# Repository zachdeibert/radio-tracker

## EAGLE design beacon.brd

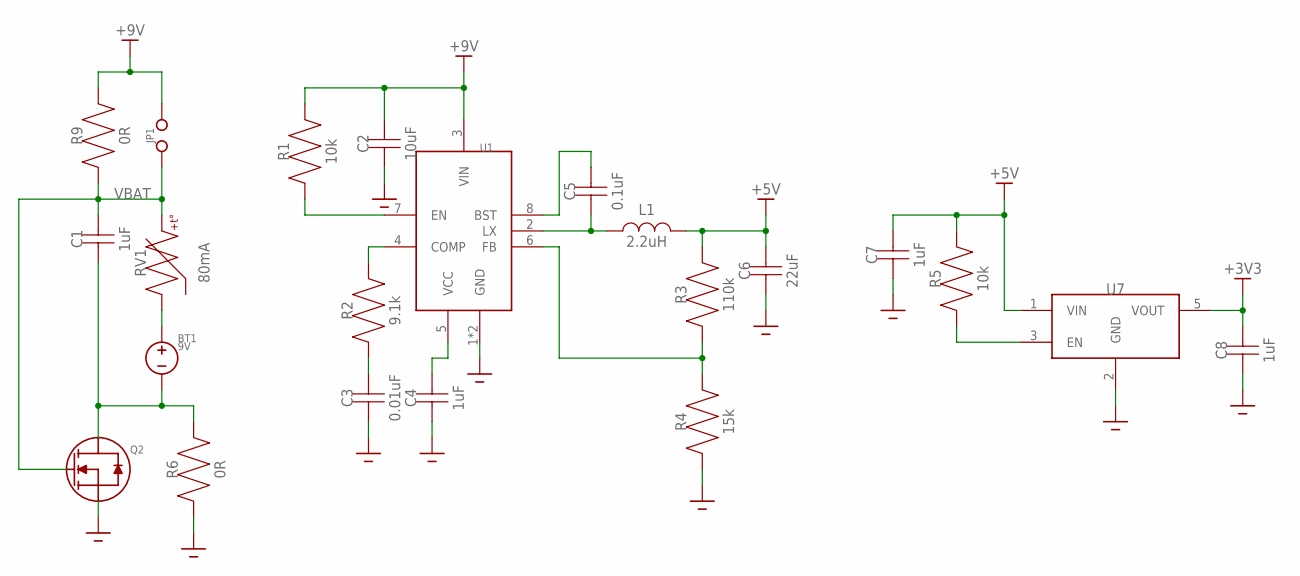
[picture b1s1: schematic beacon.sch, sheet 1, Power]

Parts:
BT1: 9V; JUMPER
C1, C4, C7, C8: 1uF; 0603
C2: 10uF; 0805
C3: 0.01uF; 0603
C5: 0.1uF; 0603
C6: 22uF; 0805
JP1: JUMPER
L1: 2.2uH; 0805
Q2: DMG2302UK
R1, R5: 10k; 0603
R2: 9.1k; 0603
R3: 110k; 0603
R4: 15k; 0603
R6, R9: 0R; 0805
RV1: 80mA; 0603
U1: AOZ6662DI
U7: MIC5504

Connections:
+3V3: C8.P$2, U7.5 (VOUT); also elsewhere on the board
+5V: C6.P$2, C7.P$2, L1.P$2, R3.P$2, R5.P$2, U7.1 (VIN); also elsewhere on the board
+9V: C2.P$2, JP1.2, R1.P$2, R9.P$2, U1.3 (VIN); also elsewhere on the board
GND: C2.P$1, C3.P$1, C4.P$1, C6.P$1, C7.P$1, C8.P$1, Q2.2 (S), R4.P$1, R6.P$1, U1.1 (GND), U1.9 (GND), U7.2 (GND); also elsewhere on the board
unnamed: R2.P$2, U1.4 (COMP)
unnamed: R1.P$1, U1.7 (EN)
unnamed: C3.P$2, R2.P$1
unnamed: C4.P$2, U1.5 (VCC)
unnamed: C5.P$2, U1.8 (BST)
unnamed: C5.P$1, L1.P$1, U1.2 (LX)
unnamed: R3.P$1, R4.P$2, U1.6 (FB)
unnamed: BT1.1, C1.P$1, Q2.3 (D), R6.P$2
unnamed: R5.P$1, U7.3 (EN)
unnamed: BT1.2, RV1.P$1
VBAT: C1.P$2, JP1.1, Q2.1 (G), R9.P$1, RV1.P$2; also elsewhere on the board

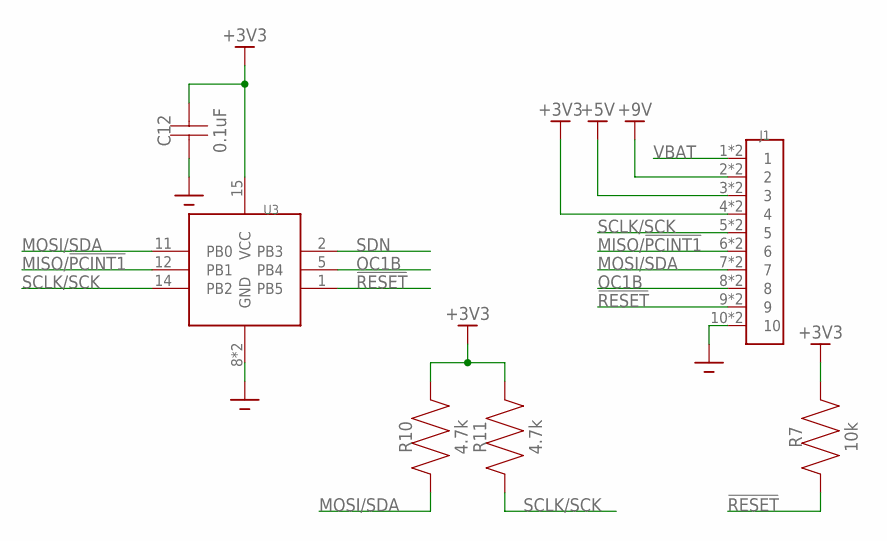
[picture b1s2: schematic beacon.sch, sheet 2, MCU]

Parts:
C12: 0.1uF; 0603
J1: 5-5530843-0MALE; 5-5530843-0-M
R7: 10k; 0603
R10, R11: 4.7k; 0603
U3: ATTINY85

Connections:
!RESET: J1.9, J1.19 (9), R7.P$1, U3.1 (PB5)
+3V3: C12.P$2, J1.4, J1.14 (4), R7.P$2, R10.P$2, R11.P$2, U3.15 (VCC); also elsewhere on the board
+5V: J1.3, J1.13 (3); also elsewhere on the board
+9V: J1.2, J1.12 (2); also elsewhere on the board
GND: C12.P$1, J1.10, J1.20 (10), U3.8 (GND), U3.21 (GND); also elsewhere on the board
MISO/!PCINT1: J1.6, J1.16 (6), U3.12 (PB1); also elsewhere on the board
MOSI/SDA: J1.7, J1.17 (7), R10.P$1, U3.11 (PB0); also elsewhere on the board
OC1B: J1.8, J1.18 (8), U3.5 (PB4); also elsewhere on the board
SCLK/SCK: J1.5, J1.15 (5), R11.P$1, U3.14 (PB2); also elsewhere on the board
SDN: U3.2 (PB3); also elsewhere on the board
VBAT: J1.1, J1.11 (1); also elsewhere on the board

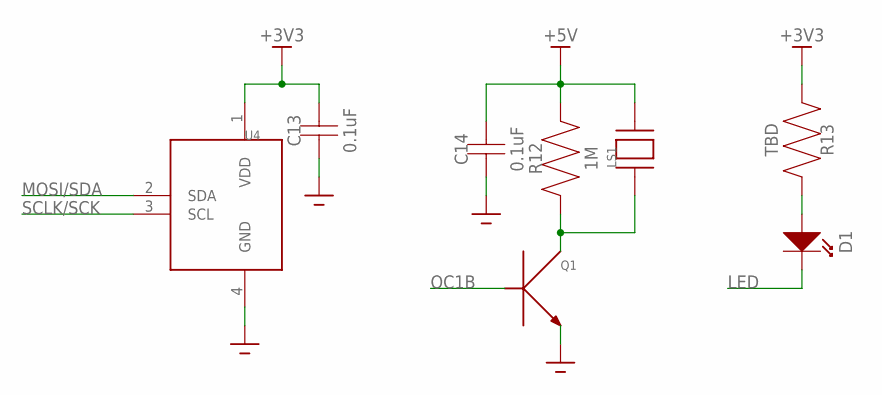
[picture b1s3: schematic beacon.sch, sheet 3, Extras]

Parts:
C13, C14: 0.1uF; 0603
D1: LED; 0805
LS1: AT-1224-TWT-5V-2-R
Q1: MMBT3904
R12: 1M; 0603
R13: TBD; 0603
U4: MS5637-02BA03

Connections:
+3V3: C13.P$2, R13.P$1, U4.1 (VDD); also elsewhere on the board
+5V: C14.P$2, LS1.2, R12.P$2; also elsewhere on the board
GND: C13.P$1, C14.P$1, Q1.2 (E), U4.4 (GND); also elsewhere on the board
LED: D1.P$2 (OUT); also elsewhere on the board
MOSI/SDA: U4.2 (SDA); also elsewhere on the board
unnamed: LS1.1, Q1.3 (C), R12.P$1
unnamed: D1.P$1 (IN), R13.P$2
OC1B: Q1.1 (B); also elsewhere on the board
SCLK/SCK: U4.3 (SCL); also elsewhere on the board

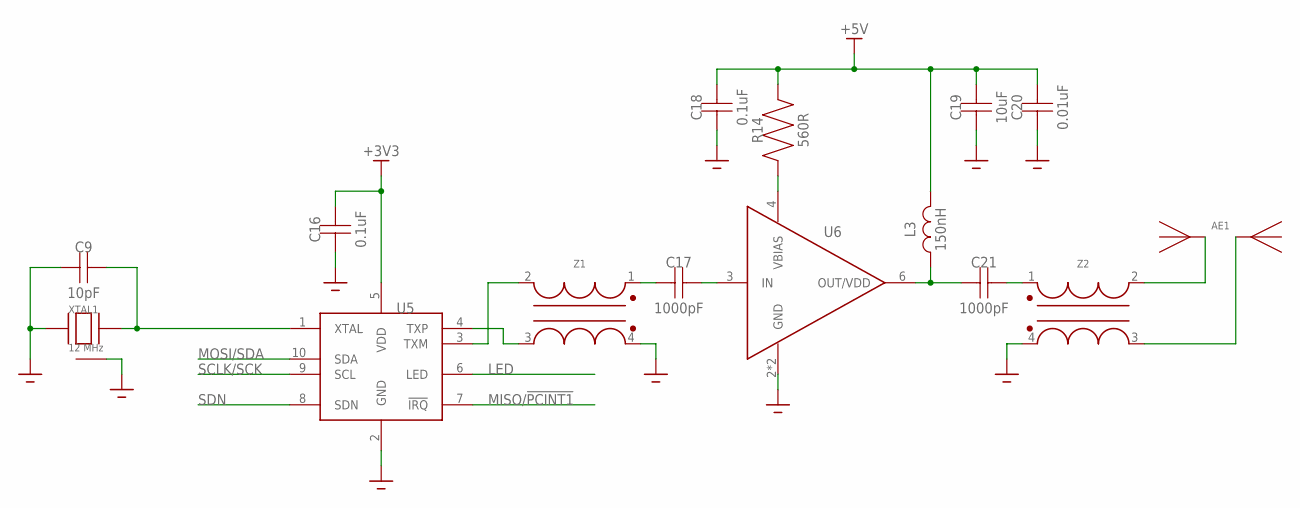
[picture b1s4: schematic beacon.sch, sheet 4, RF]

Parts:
AE1: ANTENNA
C9: 10pF; 0603
C16, C18: 0.1uF; 0603
C17, C21: 1000pF; 0402
C19: 10uF; 0603
C20: 0.01uF; 0603
L3: 150nH; 0402
R14: 560R; 0603
U5: SI4012
U6: MAAL-010704
XTAL1: 12 MHz; RH100
Z1, Z2: ABT-8

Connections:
+3V3: C16.P$2, U5.5 (VDD); also elsewhere on the board
+5V: C18.P$2, C19.P$2, C20.P$2, L3.2, R14.P$2; also elsewhere on the board
GND: C9.P$1, C16.P$1, C18.P$1, C19.P$1, C20.P$1, U5.2 (GND), U6.2 (GND), U6.5 (GND), XTAL1.1 (GND), XTAL1.2, XTAL1.3 (GND), Z1.4 (UN2), Z2.4 (UN2); also elsewhere on the board
LED: U5.6 (LED); also elsewhere on the board
MISO/!PCINT1: U5.7 (!IRQ); also elsewhere on the board
MOSI/SDA: U5.10 (SDA); also elsewhere on the board
unnamed: U5.4 (TXP), Z1.3 (BAL2)
unnamed: U5.3 (TXM), Z1.2 (BAL1)
unnamed: C9.P$2, U5.1 (XTAL), XTAL1.4
unnamed: C21.1, L3.1, U6.6 (OUT/VDD)
unnamed: C17.1, Z1.1 (UN1)
unnamed: C17.2, U6.3 (IN)
unnamed: R14.P$1, U6.4 (VBIAS)
unnamed: C21.2, Z2.1 (UN1)
unnamed: AE1.LB, AE1.LT, Z2.2 (BAL1)
unnamed: AE1.RB, AE1.RT, Z2.3 (BAL2)
SCLK/SCK: U5.9 (SCL); also elsewhere on the board
SDN: U5.8 (SDN); also elsewhere on the board

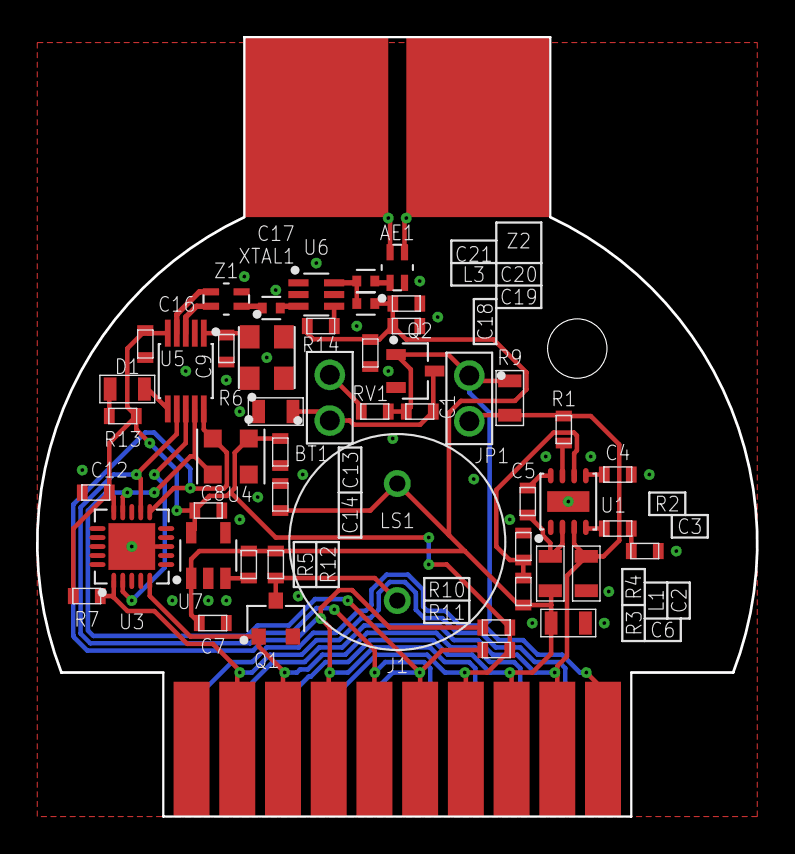
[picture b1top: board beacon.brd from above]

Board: 2 copper layers, 40.0 x 43.3 mm, 51 parts (1 on the bottom side), 34 nets.

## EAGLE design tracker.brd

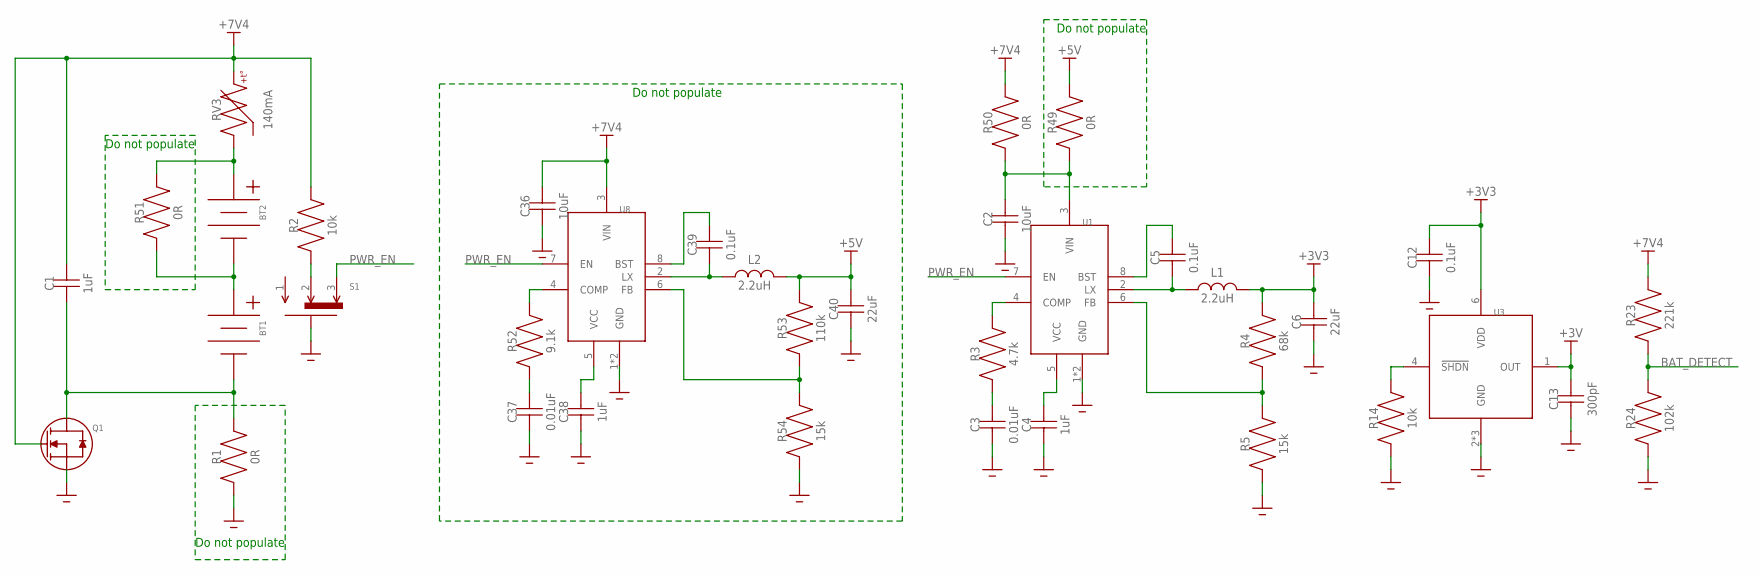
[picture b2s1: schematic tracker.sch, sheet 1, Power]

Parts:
BT1, BT2: 18650
C1, C4, C38: 1uF; 0603
C2, C36: 10uF; 0805
C3, C37: 0.01uF; 0603
C5, C12, C39: 0.1uF; 0603
C6, C40: 22uF; 0805
C13: 300pF; 0603
L1, L2: 2.2uH; 0805
Q1: DMG2302UK
R1, R49, R50, R51: 0R; 0603
R2, R14: 10k; 0603
R3: 4.7k; 0603
R4: 68k; 0603
R5, R54: 15k; 0603
R23: 221k; 0603
R24: 102k; 0603
R52: 9.1k; 0603
R53: 110k; 0603
RV3: 140mA; 1812
S1: OS102011MA1QN1
U1, U8: AOZ6662DI
U3: MCP1501; SOT95P280X145-6N

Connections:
+3V: C13.P$2, U3.1 (OUT); also elsewhere on the board
+3V3: C6.P$2, C12.P$2, L1.P$2, R4.P$2, U3.6 (VDD); also elsewhere on the board
+5V: C40.P$2, L2.P$2, R49.P$2, R53.P$2; also elsewhere on the board
+7V4V: C1.P$2, C36.P$2, Q1.1 (G), R2.P$2, R23.P$2, R50.P$2, RV3.P$2, U8.3 (VIN)
BAT_DETECT: R23.P$1, R24.P$2; also elsewhere on the board
GND: C2.P$1, C3.P$1, C4.P$1, C6.P$1, C12.P$1, C13.P$1, C36.P$1, C37.P$1, C38.P$1, C40.P$1, Q1.2 (S), R1.P$1, R5.P$1, R14.P$1, R24.P$1, R54.P$1, S1.S1 (GND), S1.S2 (GND), U1.1 (GND), U1.9 (GND), U3.2 (GND), U3.3 (GND), U3.5 (GND), U8.1 (GND), U8.9 (GND); also elsewhere on the board
unnamed: BT1.-1 (-), BT1.-2 (-), BT1.-3 (-), C1.P$1, Q1.3 (D), R1.P$2
unnamed: R3.P$2, U1.4 (COMP)
unnamed: BT1.+1 (+), BT1.+2 (+), BT1.+3 (+), BT2.-1 (-), BT2.-2 (-), BT2.-3 (-), R51.P$1
unnamed: C3.P$2, R3.P$1
unnamed: C4.P$2, U1.5 (VCC)
unnamed: C5.P$2, U1.8 (BST)
unnamed: C5.P$1, L1.P$1, U1.2 (LX)
unnamed: R4.P$1, R5.P$2, U1.6 (FB)
unnamed: R2.P$1, S1.2
unnamed: R14.P$2, U3.4 (!SHDN)
unnamed: R52.P$2, U8.4 (COMP)
unnamed: C2.P$2, R49.P$1, R50.P$1, U1.3 (VIN)
unnamed: C37.P$2, R52.P$1
unnamed: C38.P$2, U8.5 (VCC)
unnamed: C39.P$2, U8.8 (BST)
unnamed: C39.P$1, L2.P$1, U8.2 (LX)
unnamed: R53.P$1, R54.P$2, U8.6 (FB)
unnamed: BT2.+1 (+), BT2.+2 (+), BT2.+3 (+), R51.P$2, RV3.P$1
PWR_EN: S1.3, U1.7 (EN), U8.7 (EN)

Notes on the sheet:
Do not populate

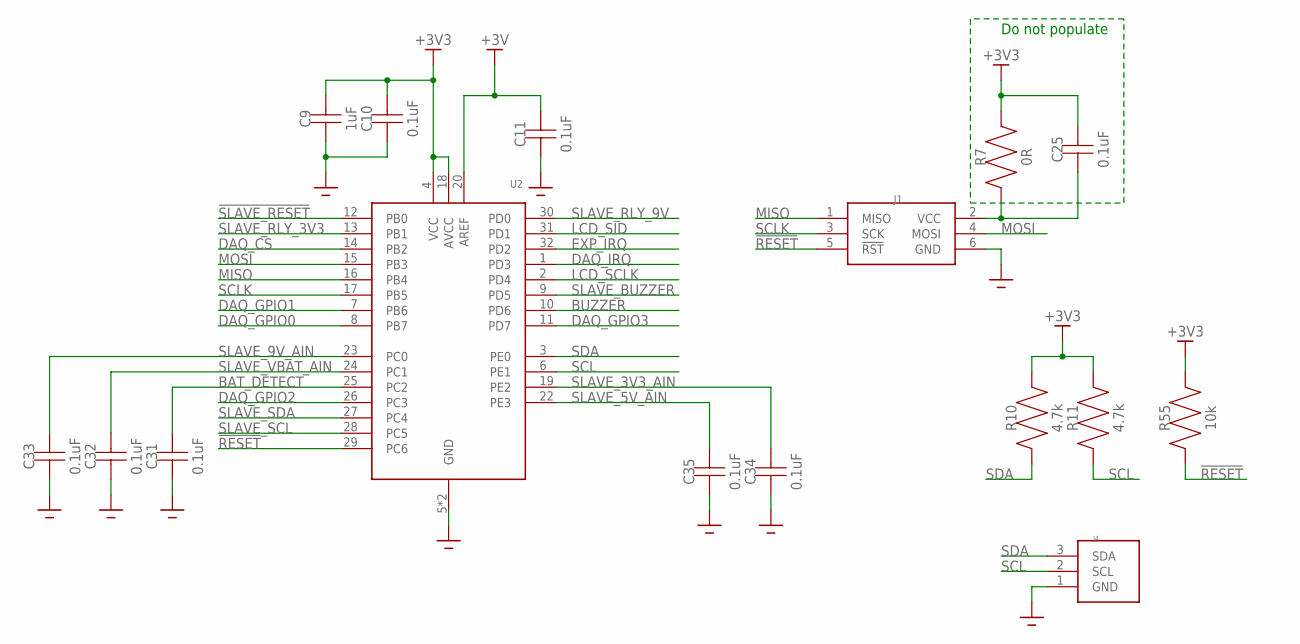
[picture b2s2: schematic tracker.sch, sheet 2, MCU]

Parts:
C9: 1uF; 0603
C10, C11, C25, C31, C32, C33, C34, C35: 0.1uF; 0603
J1: 75869-131LF
J4: 640456-3
R7: 0R; 0603
R10, R11: 4.7k; 0603
R55: 10k; 0603
U2: ATMEGA328PB32-TQFP; ATMEGA328PB

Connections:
!RESET: J1.5 (!RST), R55.P$1, U2.29 (PC6)
!SLAVE_RESET: U2.12 (PB0); also elsewhere on the board
+3V: C11.P$2, U2.20 (AREF); also elsewhere on the board
+3V3: C9.P$2, C10.P$2, C25.P$2, R7.P$2, R10.P$2, R11.P$2, R55.P$2, U2.4 (VCC), U2.18 (AVCC); also elsewhere on the board
BAT_DETECT: C31.P$2, U2.25 (PC2); also elsewhere on the board
BUZZER: U2.10 (PD6); also elsewhere on the board
DAQ_CS: U2.14 (PB2); also elsewhere on the board
DAQ_GPIO0: U2.8 (PB7); also elsewhere on the board
DAQ_GPIO1: U2.7 (PB6); also elsewhere on the board
DAQ_GPIO2: U2.26 (PC3); also elsewhere on the board
DAQ_GPIO3: U2.11 (PD7); also elsewhere on the board
DAQ_IRQ: U2.1 (PD3); also elsewhere on the board
EXP_IRQ: U2.32 (PD2); also elsewhere on the board
GND: C9.P$1, C10.P$1, C11.P$1, C31.P$1, C32.P$1, C33.P$1, C34.P$1, C35.P$1, J1.6 (GND), J4.1 (GND), U2.5 (GND), U2.21 (GND); also elsewhere on the board
LCD_SCLK: U2.2 (PD4); also elsewhere on the board
LCD_SID: U2.31 (PD1); also elsewhere on the board
MISO: J1.1 (MISO), U2.16 (PB4); also elsewhere on the board
MOSI: J1.4 (MOSI), U2.15 (PB3); also elsewhere on the board
unnamed: C25.P$1, J1.2 (VCC), R7.P$1
SCL: J4.2 (SCL), R11.P$1, U2.6 (PE1); also elsewhere on the board
SCLK: J1.3 (SCK), U2.17 (PB5); also elsewhere on the board
SDA: J4.3 (SDA), R10.P$1, U2.3 (PE0); also elsewhere on the board
SLAVE_3V3_AIN: C34.P$2, U2.19 (PE2); also elsewhere on the board
SLAVE_5V_AIN: C35.P$2, U2.22 (PE3); also elsewhere on the board
SLAVE_9V_AIN: C33.P$2, U2.23 (PC0); also elsewhere on the board
SLAVE_BUZZER: U2.9 (PD5); also elsewhere on the board
SLAVE_RLY_3V3: U2.13 (PB1); also elsewhere on the board
SLAVE_RLY_9V: U2.30 (PD0); also elsewhere on the board
SLAVE_SCL: U2.28 (PC5); also elsewhere on the board
SLAVE_SDA: U2.27 (PC4); also elsewhere on the board
SLAVE_VBAT_AIN: C32.P$2, U2.24 (PC1); also elsewhere on the board

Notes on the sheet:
Do not populate

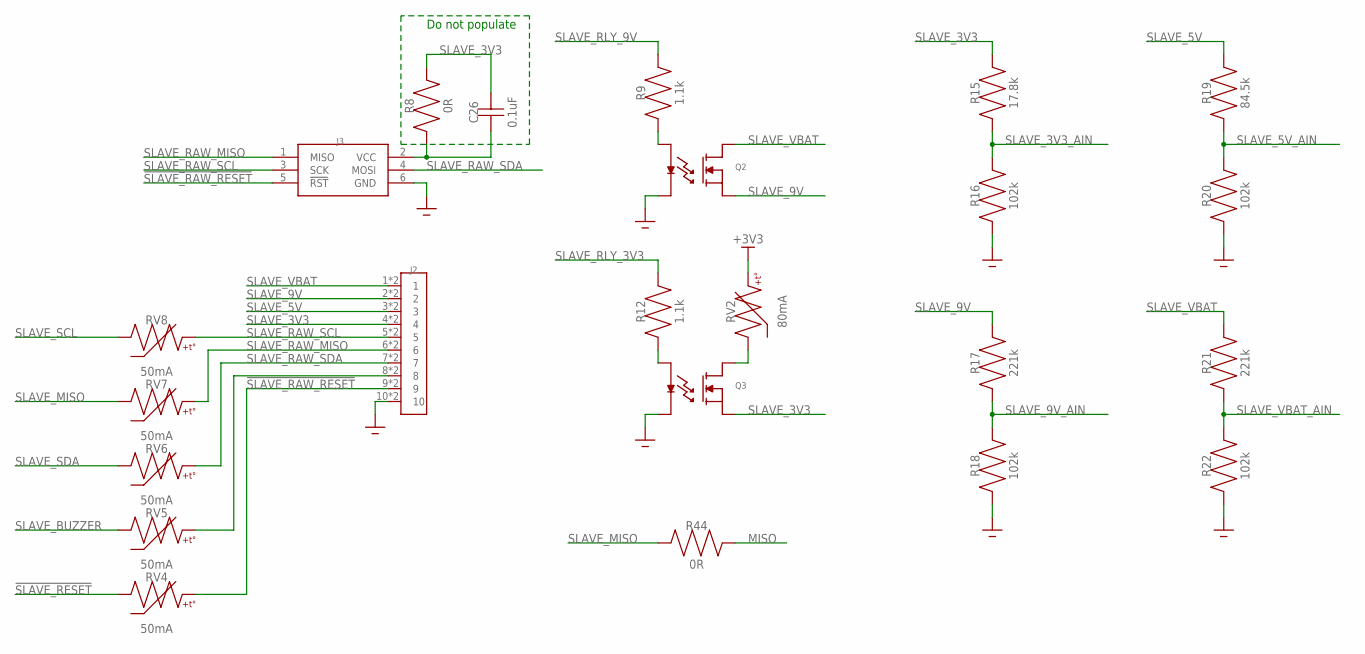
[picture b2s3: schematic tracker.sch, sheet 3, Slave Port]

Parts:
C26: 0.1uF; 0603
J2: 5-5530843-0FEMALE; 5-5530843-0
J3: 75869-131LF
Q2, Q3: CPC1002N
R8, R44: 0R; 0603
R9, R12: 1.1k; 0603
R15: 17.8k; 0603
R16, R18, R20, R22: 102k; 0603
R17, R21: 221k; 0603
R19: 84.5k; 0603
RV2: 80mA; 0603
RV4, RV5, RV6, RV7, RV8: 50mA; 0603

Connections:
!SLAVE_RAW_RESET: J2.9, J2.19 (9), J3.5 (!RST), RV4.P$2
!SLAVE_RESET: RV4.P$1; also elsewhere on the board
+3V3: RV2.P$2; also elsewhere on the board
GND: J2.10, J2.20 (10), J3.6 (GND), Q2.2 (C-), Q3.2 (C-), R16.P$1, R18.P$1, R20.P$1, R22.P$1; also elsewhere on the board
MISO: R44.P$2; also elsewhere on the board
unnamed: Q3.4 (DC+), RV2.P$1
unnamed: C26.P$1, J3.2 (VCC), R8.P$1
unnamed: Q3.1 (C+), R12.P$1
unnamed: Q2.1 (C+), R9.P$1
unnamed: J2.8, J2.18 (8), RV5.P$2
SLAVE_3V3: C26.P$2, J2.4, J2.14 (4), Q3.3 (DC-), R8.P$2, R15.P$2
SLAVE_3V3_AIN: R15.P$1, R16.P$2; also elsewhere on the board
SLAVE_5V: J2.3, J2.13 (3), R19.P$2
SLAVE_5V_AIN: R19.P$1, R20.P$2; also elsewhere on the board
SLAVE_9V: J2.2, J2.12 (2), Q2.3 (DC-), R17.P$2
SLAVE_9V_AIN: R17.P$1, R18.P$2; also elsewhere on the board
SLAVE_BUZZER: RV5.P$1; also elsewhere on the board
SLAVE_MISO: R44.P$1, RV7.P$1
SLAVE_RAW_MISO: J2.6, J2.16 (6), J3.1 (MISO), RV7.P$2
SLAVE_RAW_SCL: J2.5, J2.15 (5), J3.3 (SCK), RV8.P$2
SLAVE_RAW_SDA: J2.7, J2.17 (7), J3.4 (MOSI), RV6.P$2
SLAVE_RLY_3V3: R12.P$2; also elsewhere on the board
SLAVE_RLY_9V: R9.P$2; also elsewhere on the board
SLAVE_SCL: RV8.P$1; also elsewhere on the board
SLAVE_SDA: RV6.P$1; also elsewhere on the board
SLAVE_VBAT: J2.1, J2.11 (1), Q2.4 (DC+), R21.P$2
SLAVE_VBAT_AIN: R21.P$1, R22.P$2; also elsewhere on the board

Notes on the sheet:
Do not populate

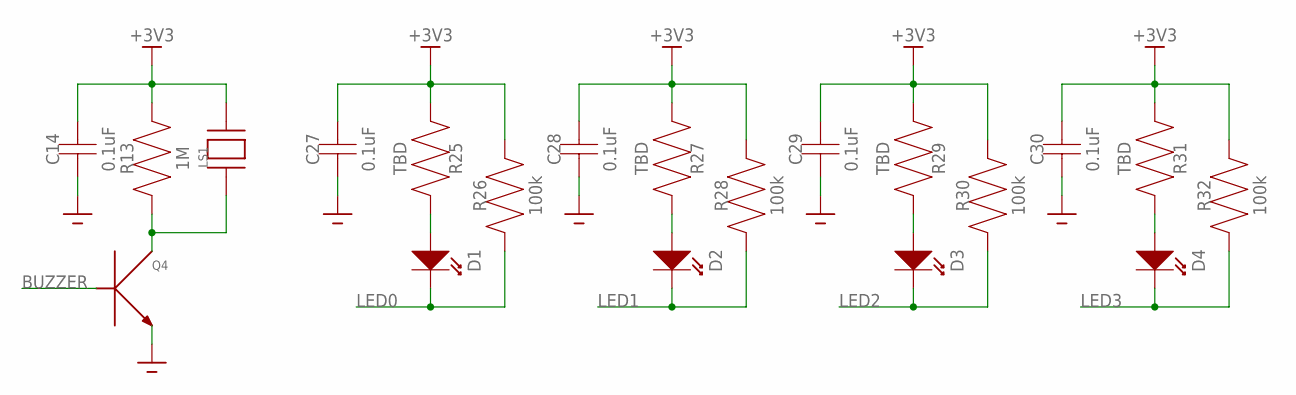
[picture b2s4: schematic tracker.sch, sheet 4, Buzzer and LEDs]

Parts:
C14, C27, C28, C29, C30: 0.1uF; 0603
D1, D2, D3, D4: LED; 0805
LS1: AT-1224-TWT-5V-2-R
Q4: MMBT3904
R13: 1M; 0603
R25, R27, R29, R31: TBD; 0603
R26, R28, R30, R32: 100k; 0603

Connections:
+3V3: C14.P$2, C27.P$2, C28.P$2, C29.P$2, C30.P$2, LS1.2, R13.P$2, R25.P$1, R26.P$2, R27.P$1, R28.P$2, R29.P$1, R30.P$2, R31.P$1, R32.P$2; also elsewhere on the board
BUZZER: Q4.1 (B); also elsewhere on the board
GND: C14.P$1, C27.P$1, C28.P$1, C29.P$1, C30.P$1, Q4.2 (E); also elsewhere on the board
LED0: D1.P$2 (OUT), R26.P$1; also elsewhere on the board
LED1: D2.P$2 (OUT), R28.P$1; also elsewhere on the board
LED2: D3.P$2 (OUT), R30.P$1; also elsewhere on the board
LED3: D4.P$2 (OUT), R32.P$1; also elsewhere on the board
unnamed: D2.P$1 (IN), R27.P$2
unnamed: D3.P$1 (IN), R29.P$2
unnamed: D1.P$1 (IN), R25.P$2
unnamed: D4.P$1 (IN), R31.P$2
unnamed: LS1.1, Q4.3 (C), R13.P$1

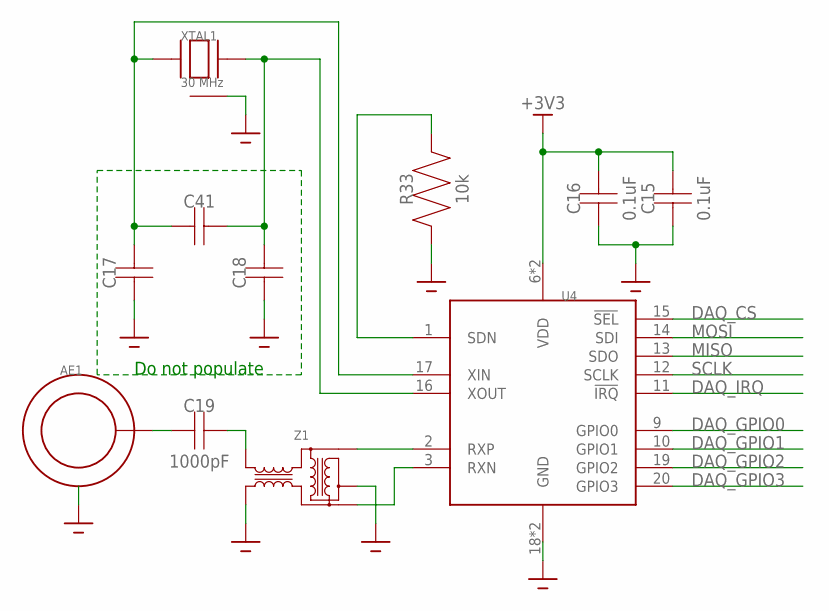
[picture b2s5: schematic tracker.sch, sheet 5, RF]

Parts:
AE1: CON-SMA-EDGE-S
C15, C16: 0.1uF; 0603
C17, C18, C41: CAPACITOR0603; 0603
C19: 1000pF; 0402
R33: 10k; 0603
U4: SI4362
XTAL1: 30 MHz; RH100
Z1: TC1-1T-152X+

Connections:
+3V3: C15.P$2, C16.P$2, U4.6 (VDD), U4.8 (VDD); also elsewhere on the board
DAQ_CS: U4.15 (!SEL); also elsewhere on the board
DAQ_GPIO0: U4.9 (GPIO0); also elsewhere on the board
DAQ_GPIO1: U4.10 (GPIO1); also elsewhere on the board
DAQ_GPIO2: U4.19 (GPIO2); also elsewhere on the board
DAQ_GPIO3: U4.20 (GPIO3); also elsewhere on the board
DAQ_IRQ: U4.11 (!IRQ); also elsewhere on the board
GND: AE1.GND1 (GND), AE1.GND2 (GND), AE1.GND3 (GND), AE1.GND4 (GND), C15.P$1, C16.P$1, C17.P$1, C18.P$1, R33.P$1, U4.18 (GND), U4.21 (GND), XTAL1.1 (GND), XTAL1.3 (GND), Z1.2 (CENTER), Z1.4 (GND); also elsewhere on the board
MISO: U4.13 (SDO); also elsewhere on the board
MOSI: U4.14 (SDI); also elsewhere on the board
unnamed: R33.P$2, U4.1 (SDN)
unnamed: AE1.CENTER (OUT), C19.1
unnamed: C17.P$2, C41.P$1, U4.17 (XIN), XTAL1.2
unnamed: U4.3 (RXN), Z1.3 (BAL2)
unnamed: U4.2 (RXP), Z1.1 (BAL1)
unnamed: C18.P$2, C41.P$2, U4.16 (XOUT), XTAL1.4
unnamed: C19.2, Z1.6 (UNBAL)
SCLK: U4.12 (SCLK); also elsewhere on the board

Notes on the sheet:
Do not populate

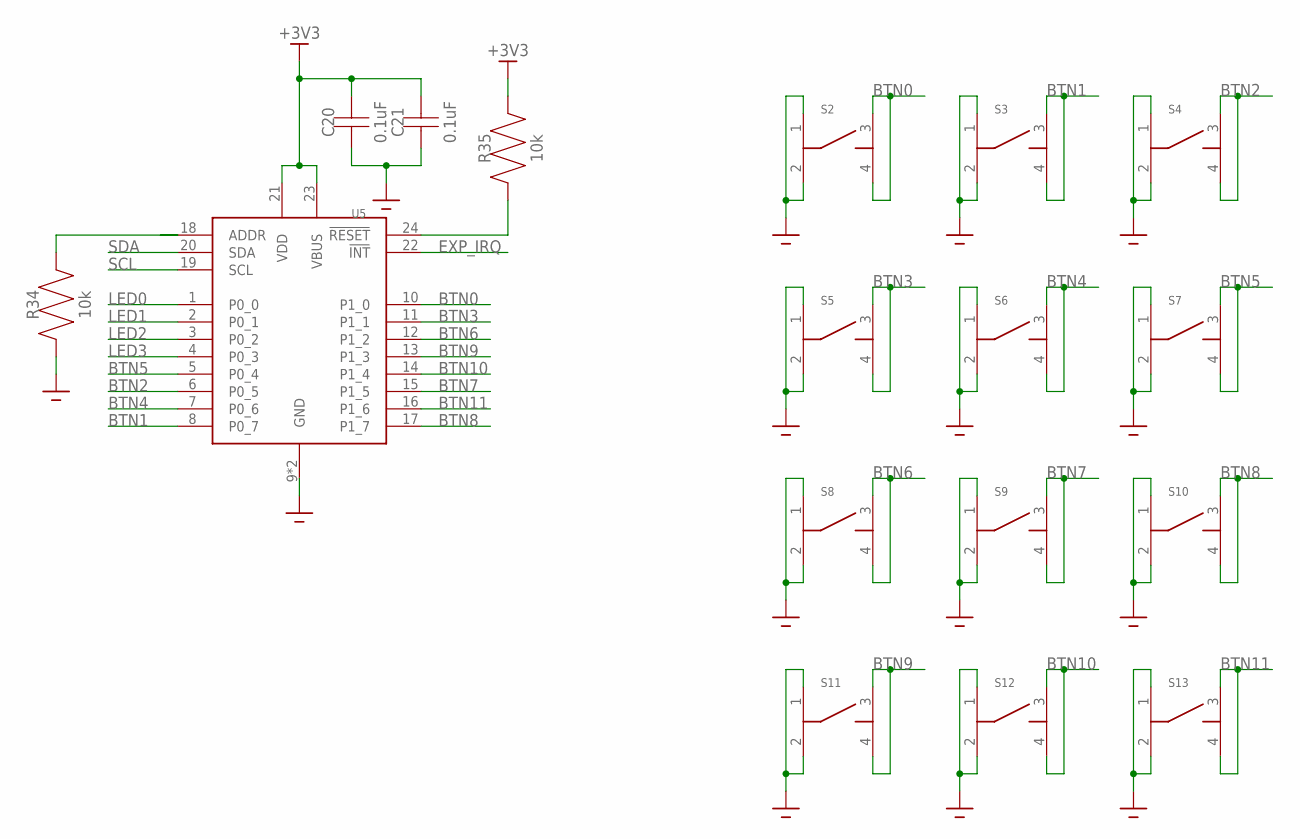
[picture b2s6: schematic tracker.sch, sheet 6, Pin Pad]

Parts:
C20, C21: 0.1uF; 0603
R34, R35: 10k; 0603
S2, S3, S4, S5, S6, S7, S8, S9, S10, S11, S12, S13: 3-1825910
U5: PCAL6416

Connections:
+3V3: C20.P$2, C21.P$2, R35.P$2, U5.21 (VDD), U5.23 (VBUS); also elsewhere on the board
BTN0: S2.3 (4), S2.4 (3), U5.10 (P1_0)
BTN1: S3.3 (4), S3.4 (3), U5.8 (P0_7)
BTN2: S4.3 (4), S4.4 (3), U5.6 (P0_5)
BTN3: S5.3 (4), S5.4 (3), U5.11 (P1_1)
BTN4: S6.3 (4), S6.4 (3), U5.7 (P0_6)
BTN5: S7.3 (4), S7.4 (3), U5.5 (P0_4)
BTN6: S8.3 (4), S8.4 (3), U5.12 (P1_2)
BTN7: S9.3 (4), S9.4 (3), U5.15 (P1_5)
BTN8: S10.3 (4), S10.4 (3), U5.17 (P1_7)
BTN9: S11.3 (4), S11.4 (3), U5.13 (P1_3)
BTN10: S12.3 (4), S12.4 (3), U5.14 (P1_4)
BTN11: S13.3 (4), S13.4 (3), U5.16 (P1_6)
EXP_IRQ: U5.22 (!INT); also elsewhere on the board
GND: C20.P$1, C21.P$1, R34.P$1, S2.1, S2.2, S3.1, S3.2, S4.1, S4.2, S5.1, S5.2, S6.1, S6.2, S7.1, S7.2, S8.1, S8.2, S9.1, S9.2, S10.1, S10.2, S11.1, S11.2, S12.1, S12.2, S13.1, S13.2, U5.9 (GND), U5.25 (GND); also elsewhere on the board
LED0: U5.1 (P0_0); also elsewhere on the board
LED1: U5.2 (P0_1); also elsewhere on the board
LED2: U5.3 (P0_2); also elsewhere on the board
LED3: U5.4 (P0_3); also elsewhere on the board
unnamed: R35.P$1, U5.24 (!RESET)
unnamed: R34.P$2, U5.18 (ADDR)
SCL: U5.19 (SCL); also elsewhere on the board
SDA: U5.20 (SDA); also elsewhere on the board

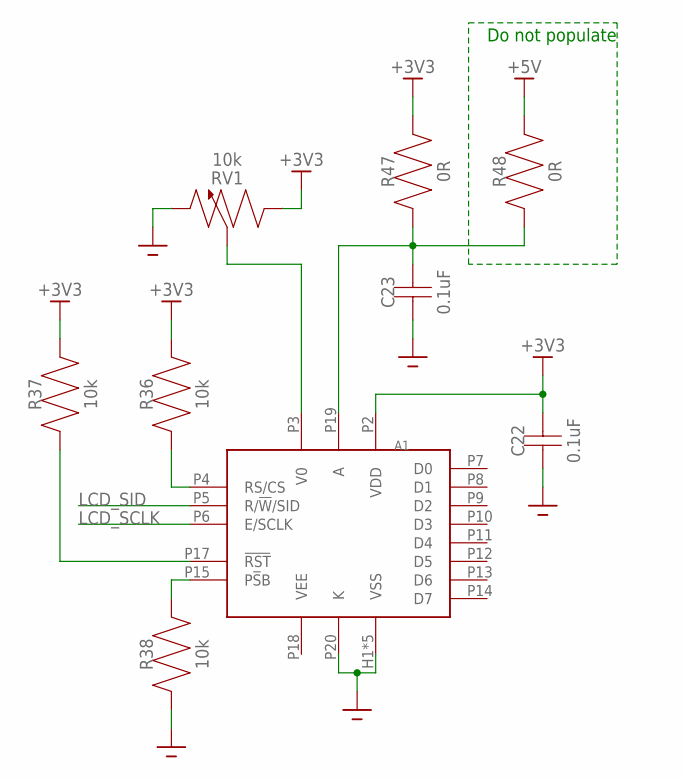
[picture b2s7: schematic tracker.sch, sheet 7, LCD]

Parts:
A1: LCD12864
C22, C23: 0.1uF; 0603
R36, R37, R38: 10k; 0603
R47, R48: 0R; 0603
RV1: 10k; TC33X-2

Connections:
+3V3: A1.P2 (VDD), C22.P$2, R36.P$2, R37.P$2, R47.P$2, RV1.1 (CCW); also elsewhere on the board
+5V: R48.P$2; also elsewhere on the board
GND: A1.H1 (VSS), A1.H2 (VSS), A1.H3 (VSS), A1.H4 (VSS), A1.P1 (VSS), A1.P20 (K), C22.P$1, C23.P$1, R38.P$1, RV1.3 (CW); also elsewhere on the board
LCD_SCLK: A1.P6 (E/SCLK); also elsewhere on the board
LCD_SID: A1.P5 (R/!W!/SID); also elsewhere on the board
unnamed: A1.P4 (RS/CS), R36.P$1
unnamed: A1.P17 (!RST), R37.P$1
unnamed: A1.P15 (P!S!B), R38.P$2
unnamed: A1.P3 (V0), RV1.2 (WIPER)
unnamed: A1.P19 (A), C23.P$2, R47.P$1, R48.P$1
VEE: A1.P18 (VEE)

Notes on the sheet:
Do not populate

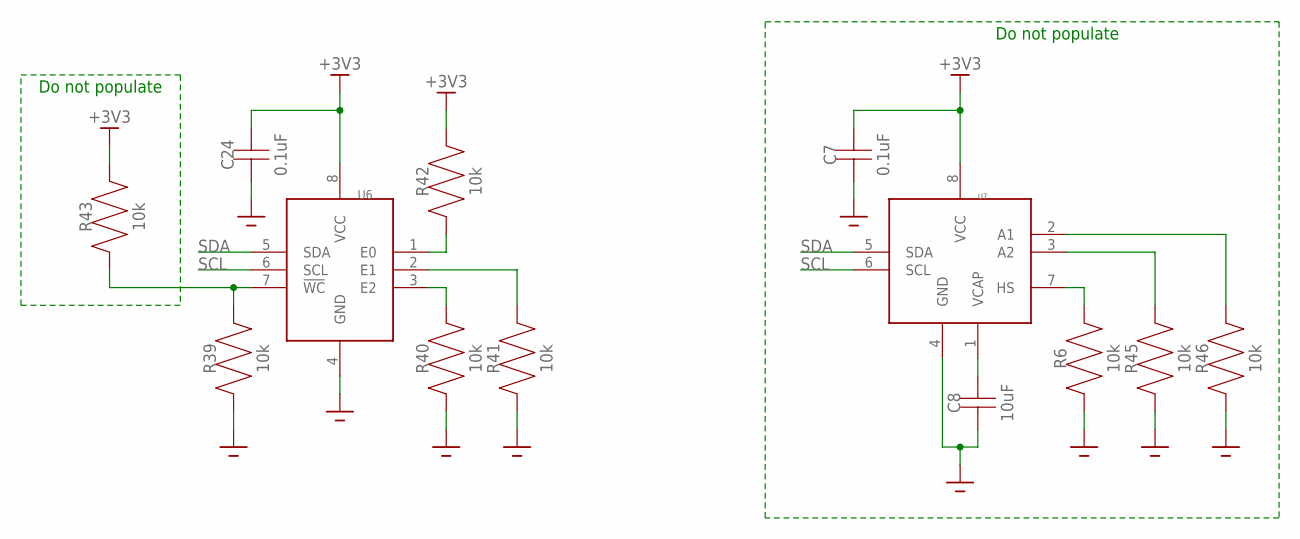
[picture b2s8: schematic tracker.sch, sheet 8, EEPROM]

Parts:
C7, C24: 0.1uF; 0603
C8: 10uF; 0805
R6, R39, R40, R41, R42, R43, R45, R46: 10k; 0603
U6: M24
U7: 47L16

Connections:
+3V3: C7.P$2, C24.P$2, R42.P$2, R43.P$2, U6.8 (VCC), U7.8 (VCC); also elsewhere on the board
GND: C7.P$1, C8.P$1, C24.P$1, R6.P$1, R39.P$1, R40.P$1, R41.P$1, R45.P$1, R46.P$1, U6.4 (GND), U7.4 (GND); also elsewhere on the board
unnamed: R42.P$1, U6.1 (E0)
unnamed: R39.P$2, R43.P$1, U6.7 (!WC)
unnamed: R40.P$2, U6.3 (E2)
unnamed: R41.P$2, U6.2 (E1)
unnamed: R6.P$2, U7.7 (HS)
unnamed: C8.P$2, U7.1 (VCAP)
unnamed: R45.P$2, U7.3 (A2)
unnamed: R46.P$2, U7.2 (A1)
SCL: U6.6 (SCL), U7.6 (SCL); also elsewhere on the board
SDA: U6.5 (SDA), U7.5 (SDA); also elsewhere on the board

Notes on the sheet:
Do not populate

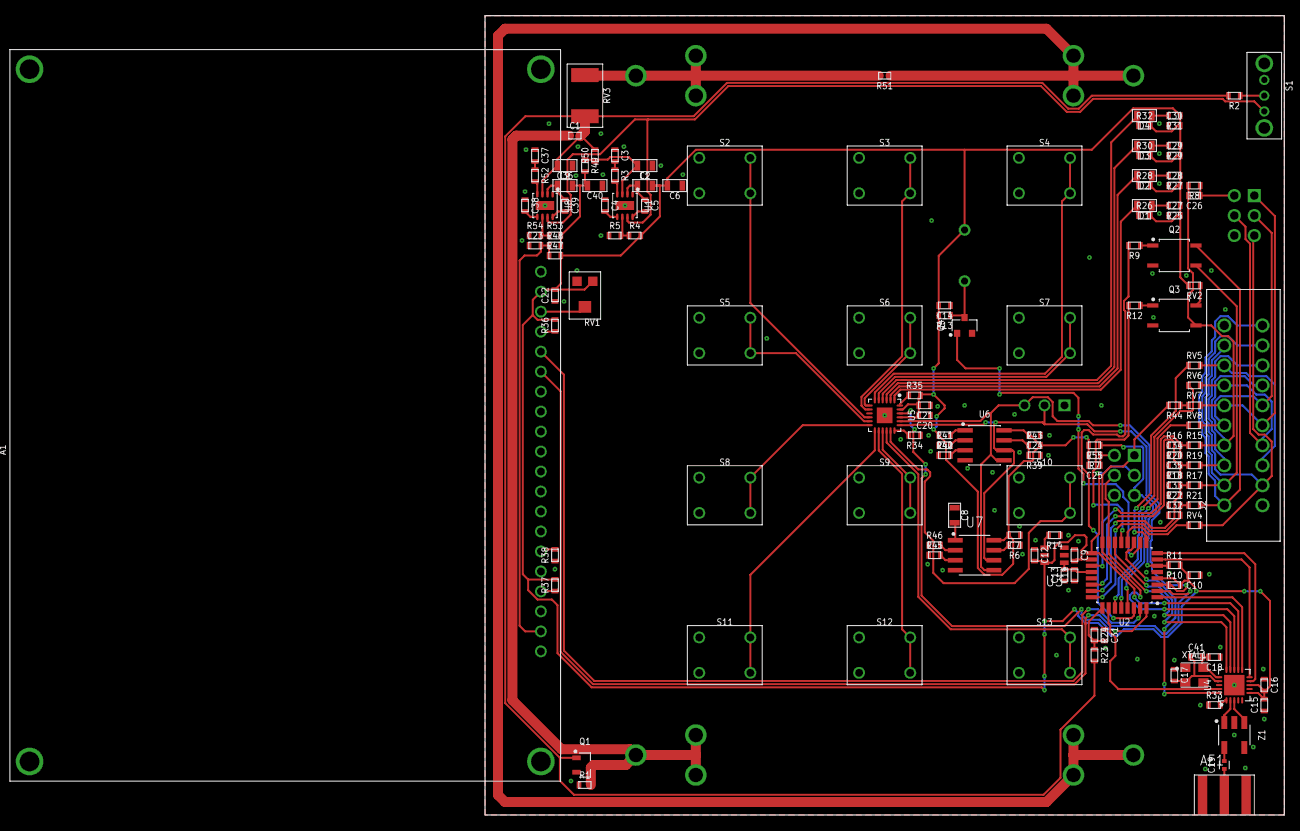
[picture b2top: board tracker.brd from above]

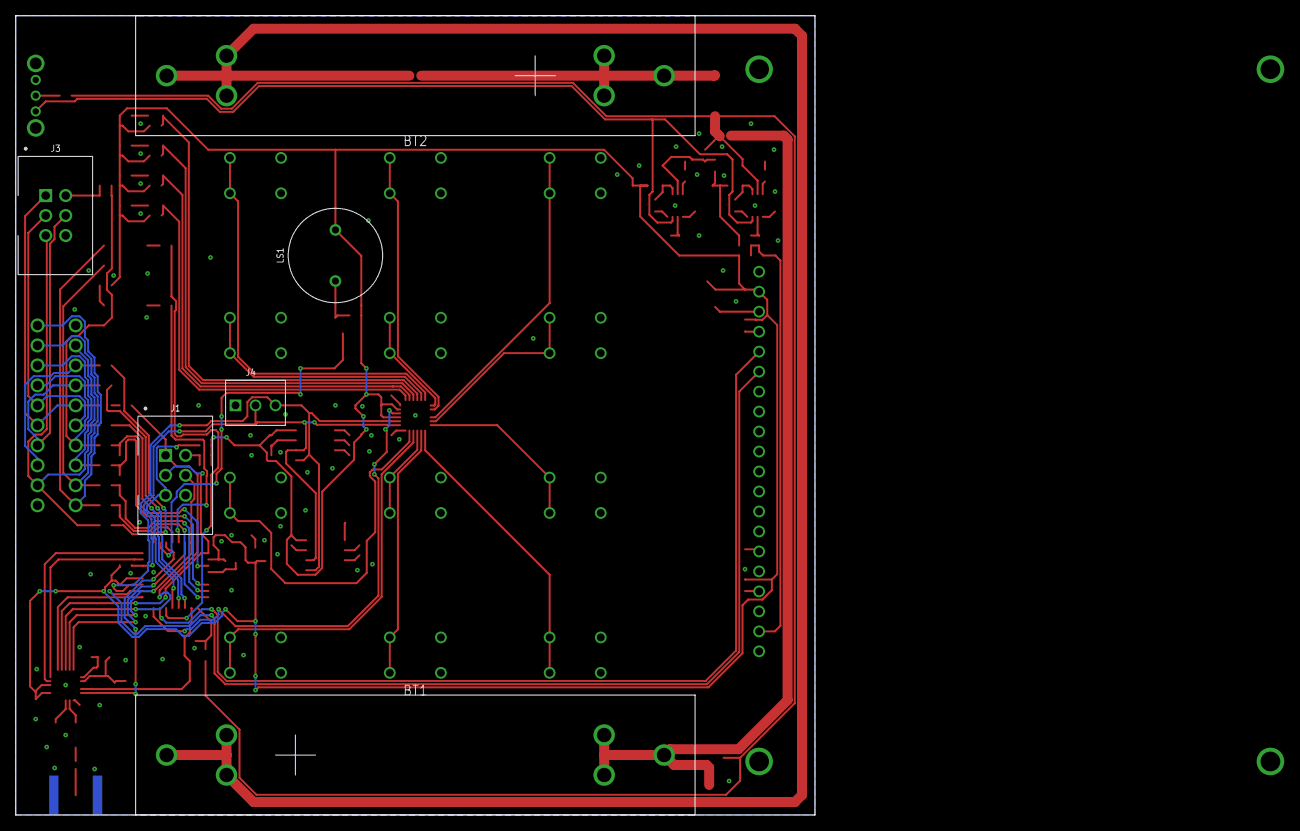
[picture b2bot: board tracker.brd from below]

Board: 2 copper layers, 101.6 x 101.6 mm, 146 parts (6 on the bottom side), 109 nets.

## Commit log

2020-05-21 Created initial schematic for beacon
2020-05-22 Initial version of tracker schematic
2020-05-23 Various schematic updates
2020-05-26 A few schematic updates
2020-06-21 First routing attempt
2020-06-21 Routed beacon
2020-06-21 Fixed silk screen on beacon
2020-06-21 Added PTC fuse
2020-06-22 Layed out tracker board
2020-06-27 Added skeleton for code
2020-06-28 Started to write GIMP plugin
2020-06-28 Wrote simple version of the EEPROM generator
